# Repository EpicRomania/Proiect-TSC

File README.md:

# Proiect-TSC

## Block Diagram

## ESP32-C6

Microcontrolerul central care coordoneaza procesarea datelor si comunicarea cu modulele.
- Microcontroler RISC-V cu Wi-Fi 6 și Bluetooth LE.
  
**Controleaza interfetele SPI si I2C pentru restul modulelor.**

**Pentru conectarea memoriei externe, sunt folositi urmatorii pini:**

- MOSI  
- MISO  
- SCK  
- CS

**Pentru conectarea ceasului real si a senzorilor, se utilizeaza:**

- SDA  
- SCL

**Pinii de debug si programare sunt accesibili prin interfata dedicata.**

## Memorie Externa

- Conectata prin SPI (MOSI, MISO, SCK, CS). 

- Stocheaza datele e-book si firmware-ul.

## Ceas Real si Module Senzoriale

- Dispozitivele de timp real si senzorii se conecteaza pe pinii SDA si SCL.
- **DS3231** pentru data/ora precisa (RTC).  
- **BME680/BME688** pentru temperatura, umiditate, presiune si VOC (aer). 
- Aceste module asigura sincronizarea si monitorizarea mediului.

## Afisaj E-Paper 
- Controlat prin interfata SPI (linii comune cu memoria externa, dar cu semnal CS separat).  
- Are propriul circuit driver (bobina L2 si componente auxiliare).

## Stocare pe card SD
- Conectat tot pe magistrala SPI pentru extinderea posibilitatilor de stocare

 ## Butoane  
- **Reset** si **Boot** pentru controlul microcontrolerului (reprogramare, reset).
- **Change** – buton suplimentar pentru interactiuni in aplicatie.

## Management Baterie
- **MCP73831** ca incarcator LiPo (5 V din USB-C -> LiPo).  
- **MAX17048** ca monitor de nivel al bateriei (I2C).  
- **USB-C** pentru alimentare, incarcare si, la nevoie, date USB.

## Aspecte de Design

- Componentele sunt asezate astfel incat accesul la conectori sa fie relatic simplu.
- Test pads (TP) sunt disponibile pe fata placii pentru masuratori de semnal si alimentare.  
- Circuitele de protectie ESD si de filtrare sunt incluse pentru USB-C si liniile SPI. 

## Bill of Materials

| Component                          | Buy Link                                                                                                      | Datasheet Link                                                                                                                 |
|------------------------------------|---------------------------------------------------------------------------------------------------------------|--------------------------------------------------------------------------------------------------------------------------------|
| ADAFRUIT_LEDCHIP-LED0603           | [Mouser](https://ro.mouser.com/c/optoelectronics/led-lighting/?m=Adafruit)                                    | [Datasheet](https://ro.mouser.com/c/optoelectronics/led-lighting/?m=Adafruit)                                                  |
| SJ                                 | [GrabCAD](https://grabcad.com/library/solder-jumpers-1)                                                       | [GrabCAD](https://grabcad.com/library/solder-jumpers-1)                                                                        |
| ESP32_WROVER_EAGLE-LTSPICE_CC0402  | [Mouser](https://ro.mouser.com/c/passive-components/capacitors/ceramic-capacitors/?q=CC0402)                  | [Datasheet](https://componentsearchengine.com/Datasheets/2/CC0402MRX5R5BB106.pdf)                                              |
| ESP32_WROVER_EAGLE-LTSPICE_RR0402  | [Mouser](https://ro.mouser.com/c/passive-components/resistors/smd-resistors-chip-resistors/?case%20code%20-%20in=0402) | [Datasheet](https://www.yageo.com/upload/media/product/products/datasheet/rchip/PYu-RC_Group_51_RoHS_L_12.pdf)                 |
| RCL_CPOL-EUCT3528                  | [Mouser](https://ro.mouser.com/c/passive-components/antennas/?m=Linx+Technologies&series=RCL)                 | [Mouser](https://ro.mouser.com/c/passive-components/antennas/?m=Linx+Technologies&series=RCL)                                  |
| 112A-TAAR-R03_ATTEND               | [Comet](https://store.comet.srl.ro/Catalogue/Product/43497/)                                                   | [SnapEDA](https://www.snapeda.com/parts/112A-TAAR-R03/Attend/datasheet/)                                                       |
| DMG2305UX-7                        | [DigiKey](https://www.digikey.com/en/products/detail/diodes-incorporated/DMG2305UX-7/4340666)                 | [Datasheet](https://www.diodes.com/assets/Datasheets/DMG2305UX.pdf)                                                            |
| 744043680IND_4828-WE-TPC_WRE       | [Mouser](https://ro.mouser.com/ProductDetail/Wurth-Elektronik/744043680?qs=PGXP4M47uW6VkZq%252BkzjrHA%3D%3D)  | [Datasheet](https://www.we-online.com/components/products/datasheet/744043680.pdf)                                             |
| BME680                             | [Mouser](https://ro.mouser.com/ProductDetail/Bosch-Sensortec/BME688?qs=IS%252B4QmGtzzqQoVDscqwx3A%3D%3D)      | [Datasheet](https://ro.mouser.com/datasheet/2/783/bst_bme688_fl000-2307034.pdf)                                                |
| BUTTON_CUSYOMV1                    | [Panasonic](https://industry.panasonic.com/global/en/products/control/switch/light-touch/number/evqpuj02k)    | [Datasheet](https://industry.panasonic.com/global/en/downloads?tab=catalog&small_g_cd=203&part_no=EVQPUJ02K)                   |
| DS3231SN#                          | [Mouser](https://ro.mouser.com/ProductDetail/Analog-Devices-Maxim-Integrated/DS3231SN?qs=1eQvB6Dk1vhUlr8%2FOrV0Fw%3D%3D) | [Datasheet](https://ro.mouser.com/datasheet/2/609/DS3231-3421123.pdf)                                                          |
| ESP32-C6-WROOM-1-N8                | [Mouser](https://ro.mouser.com/ProductDetail/Espressif-Systems/ESP32-C6-WROOM-1-N8?qs=8Wlm6%252BaMh8ST02Gmwp74cw%3D%3D) | [Datasheet](https://ro.mouser.com/datasheet/2/891/Espressif_ESP32_C6_WROOM_1__Datasheet_V0_1_PRELIMI-3239987.pdf)              |
| ESP32C6_VARISTORCN1812             | [Mouser](https://ro.mouser.com/c/circuit-protection/varistors/?package=1812)                                 | [Mouser](https://ro.mouser.com/c/circuit-protection/varistors/?package=1812)                                                   |
| SD0805S020S1R0                     | [Mouser](https://ro.mouser.com/ProductDetail/KYOCERA-AVX/SD0805S020S1R0?qs=jCA%252BPfw4LHbpkAoSnwrdjw%3D%3D)  | [Datasheet](https://ro.mouser.com/datasheet/2/40/schottky-3165252.pdf)                                                         |
| MCP73831                           | [Mouser](https://ro.mouser.com/ProductDetail/Microchip-Technology/MCP73831T-2ATI-OT?qs=yUQqVecv4qsZbioEUu%252B83g%3D%3D) | [Datasheet](https://ro.mouser.com/datasheet/2/268/MCP73831_Family_Data_Sheet_DS20001984H-3441711.pdf)                          |

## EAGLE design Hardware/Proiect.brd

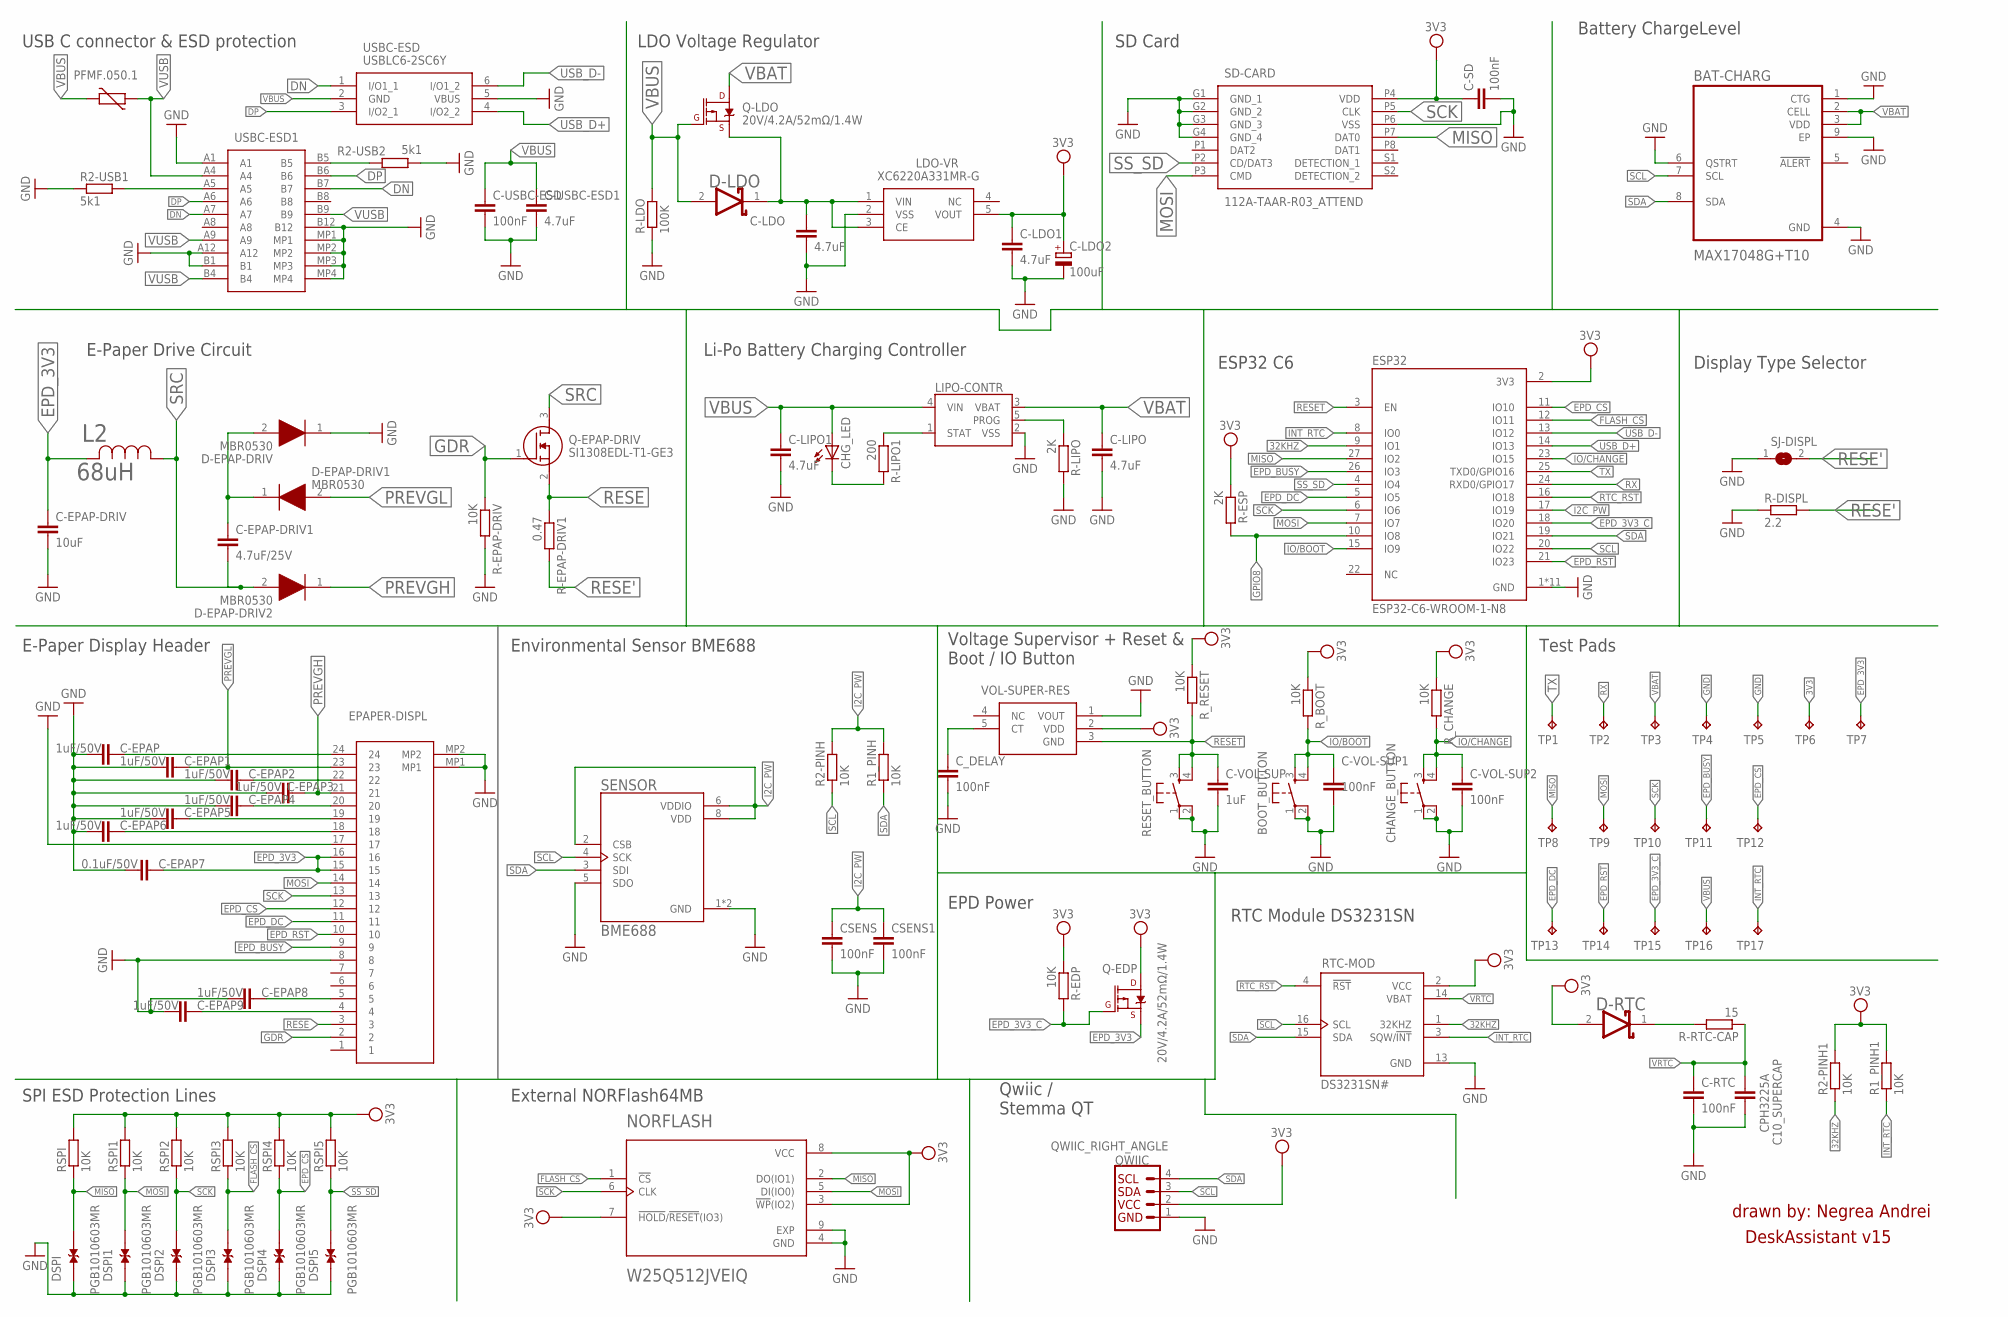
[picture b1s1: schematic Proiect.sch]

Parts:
BAT-CHARG: MAX17048G+T10; SON50P200X200X80-9N
BOOT_BUTTON: BOOT_BUTTON; MYBUTTON
C-EPAP, C-EPAP1, C-EPAP2, C-EPAP3, C-EPAP4, C-EPAP5, C-EPAP6, C-EPAP8, C-EPAP9: 1uF/50V; ESP32_WROVER_EAGLE-LTSPICE_C0402
C-EPAP7: 0.1uF/50V; ESP32_WROVER_EAGLE-LTSPICE_C0402
C-EPAP-DRIV: 10uF; ESP32_WROVER_EAGLE-LTSPICE_C0402
C-EPAP-DRIV1: 4.7uF/25V; ESP32_WROVER_EAGLE-LTSPICE_C0402
C-LDO, C-LDO1: 4.7uF; ESP32_WROVER_EAGLE-LTSPICE_C0402
C-LDO2: 100uF; RCL_CT3528
C-LIPO, C-LIPO1: 4.7uF; ESP32_WROVER_EAGLE-LTSPICE_C0402
C-RTC: 100nF; ESP32_WROVER_EAGLE-LTSPICE_C0402
C-SD: 100nF; ESP32_WROVER_EAGLE-LTSPICE_C0402
C-USBC-ESD: 100nF; ESP32_WROVER_EAGLE-LTSPICE_C0402
C-USBC-ESD1: 4.7uF; ESP32_WROVER_EAGLE-LTSPICE_C0402
C-VOL-SUP: 1uF; ESP32_WROVER_EAGLE-LTSPICE_C0402
C-VOL-SUP1, C-VOL-SUP2: 100nF; ESP32_WROVER_EAGLE-LTSPICE_C0402
CHANGE_BUTTON: CHANGE_BUTTON; MYBUTTON
CHG_LED: ADAFRUIT_LEDCHIP-LED0603; ADAFRUIT_CHIP-LED0603
CPH3225A: C10_SUPERCAP; ESP32_WROVER_EAGLE-LTSPICE_C0402
CSENS, CSENS1: 100nF; ESP32_WROVER_EAGLE-LTSPICE_C0402
C_DELAY: 100nF; ESP32_WROVER_EAGLE-LTSPICE_C0402
D-EPAP-DRIV, D-EPAP-DRIV1, D-EPAP-DRIV2: MBR0530; SOD3716X135N
D-LDO: ESP32_WROVER_AVX---SD0805S020S1R0_AVX_SD0805S020S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; ESP32_WROVER_AVX---SD0805S020S1R0_AVX_SD0805S020S1R0_0
D-RTC: ESP32_WROVER_AVX---SD0805S020S1R0_AVX_SD0805S020S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; ESP32_WROVER_AVX---SD0805S020S1R0_AVX_SD0805S020S1R0_0
DSPI, DSPI1, DSPI2, DSPI3, DSPI4, DSPI5: PGB1010603MR; DIOC1608X36N
EPAPER-DISPL: FH34SRJ-24S-0.5SH_99_; FH34SRJ24S05SH99
ESP32: ESP32-C6-WROOM-1-N8; XCVR_ESP32-C6-WROOM-1-N8
L2: 68uH; IND_4828-WE-TPC_WRE
LDO-VR: XC6220A331MR-G; SOT95P280X120-5N
LIPO-CONTR: ESP32_WROVER_SPARKFUN-IC-POWER_MCP73831; ESP32_WROVER_SPARKFUN-IC-POWER_SOT23-5
NORFLASH: W25Q512JVEIQ; SON127P600X800X80-9N
PFMF.050.1: ESP32C6_VARISTORCN1812; ESP32C6_VARISTOR_CT/CN1812
Q-EDP: 20V/4.2A/52mΩ/1.4W; ESP32_WROVER_SPARKFUN-DISCRETESEMI_SOT23-3
Q-EPAP-DRIV: SI1308EDL-T1-GE3; SOT65P210X110-3N
Q-LDO: 20V/4.2A/52mΩ/1.4W; ESP32_WROVER_SPARKFUN-DISCRETESEMI_SOT23-3
QWIIC: QWIIC_RIGHT_ANGLE; JST04_1MM_RA
R1_PINH, R1_PINH1, R2-PINH, R2-PINH1: 10K; ESP32_WROVER_EAGLE-LTSPICE_R0402
R2-USB1, R2-USB2: 5k1; ESP32_WROVER_EAGLE-LTSPICE_R0402
R-DISPL: 2.2; ESP32_WROVER_EAGLE-LTSPICE_R0402
R-EDP: 10K; ESP32_WROVER_EAGLE-LTSPICE_R0402
R-EPAP-DRIV: 10K; ESP32_WROVER_EAGLE-LTSPICE_R0402
R-EPAP-DRIV1: 0.47; ESP32_WROVER_EAGLE-LTSPICE_R0402
R-ESP: 2K; ESP32_WROVER_EAGLE-LTSPICE_R0402
R-LDO: 100K; ESP32_WROVER_EAGLE-LTSPICE_R0402
R-LIPO: 2K; ESP32_WROVER_EAGLE-LTSPICE_R0402
R-LIPO1: 200; ESP32_WROVER_EAGLE-LTSPICE_R0402
R-RTC-CAP: 15; ESP32_WROVER_EAGLE-LTSPICE_R0402
RESET_BUTTON: RESET_BUTTON; MYBUTTON
RSPI, RSPI1, RSPI2, RSPI3, RSPI4, RSPI5: 10K; ESP32_WROVER_EAGLE-LTSPICE_R0402
RTC-MOD: DS3231SN#; SOIC127P1032X265-16N
R_BOOT: 10K; ESP32_WROVER_EAGLE-LTSPICE_R0402
R_CHANGE: 10K; ESP32_WROVER_EAGLE-LTSPICE_R0402
R_RESET: 10K; ESP32_WROVER_EAGLE-LTSPICE_R0402
SD-CARD: 112A-TAAR-R03_ATTEND; 112ATAARR03ATTEND
SENSOR: BME688; ESP32_WROVER_BME680_PSON80P300X300X100-8N
SJ-DISPL: SJ
TP1, TP2, TP3, TP4, TP5, TP6, TP7, TP8, TP9, TP10, TP11, TP12, TP13, TP14, TP15, TP16, TP17: TPTP20R; TP20R
USBC-ESD: USBLC6-2SC6Y; SOT95P280X145-6N
USBC-ESD1: SAMACSYS_PARTS_USB4110-GF-A; SAMACSYS_PARTS_USB4110GFA
VOL-SUPER: VOL-SUPER-RES; SOT95P280X125-5N

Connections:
3V3: C-LDO1.1, C-LDO2.+, C-SD.1, D-RTC.2 (ANODE), ESP32.2 (3V3), LDO-VR.5 (VOUT), NORFLASH.3 (!WP!(IO2)), NORFLASH.7 (!HOLD!/!RESET!(IO3)), NORFLASH.8 (VCC), Q-EDP.3 (D), QWIIC.2, R1_PINH1.2, R2-PINH1.2, R-EDP.1, R-ESP.1, RSPI.2, RSPI1.2, RSPI2.2, RSPI3.2, RSPI4.2, RSPI5.2, RTC-MOD.2 (VCC), R_BOOT.1, R_CHANGE.1, R_RESET.1, SD-CARD.P4 (VDD), TP6.TP, VOL-SUPER.2 (VDD)
32KHZ: ESP32.9 (IO1), R2-PINH1.1, RTC-MOD.1 (32KHZ)
DN: USBC-ESD.1 (I/O1_1), USBC-ESD1.A7, USBC-ESD1.B7
DP: USBC-ESD.3 (I/O2_1), USBC-ESD1.A6, USBC-ESD1.B6
EPD_3V3: C-EPAP7.1, C-EPAP-DRIV.1, EPAPER-DISPL.15, EPAPER-DISPL.16, L2.2, Q-EDP.2 (S), TP7.TP
EPD_3V3_C: ESP32.18 (IO20), Q-EDP.1 (G), R-EDP.2, TP15.TP
EPD_BUSY: EPAPER-DISPL.9, ESP32.26 (IO3), TP11.TP
EPD_CS: DSPI4.2, EPAPER-DISPL.12, ESP32.11 (IO10), RSPI4.1, TP12.TP
EPD_DC: EPAPER-DISPL.11, ESP32.5 (IO5), TP13.TP
EPD_RST: EPAPER-DISPL.10, ESP32.21 (IO23), TP14.TP
FLASH_CS: DSPI3.2, ESP32.12 (IO11), NORFLASH.1 (!CS), RSPI3.1
GDR: EPAPER-DISPL.2, Q-EPAP-DRIV.1 (G), R-EPAP-DRIV.1
GND: BAT-CHARG.1 (CTG), BAT-CHARG.4 (GND), BAT-CHARG.6 (QSTRT), BAT-CHARG.9 (EP), BOOT_BUTTON.1, BOOT_BUTTON.2, C-EPAP.2, C-EPAP1.2, C-EPAP2.2, C-EPAP3.2, C-EPAP4.2, C-EPAP5.2, C-EPAP6.2, C-EPAP7.2, C-EPAP8.2, C-EPAP9.2, C-EPAP-DRIV.2, C-LDO.2, C-LDO1.2, C-LDO2.-, C-LIPO.2, C-LIPO1.2, C-RTC.2, C-SD.2, C-USBC-ESD.2, C-USBC-ESD1.2, C-VOL-SUP.2, C-VOL-SUP1.2, C-VOL-SUP2.2, CHANGE_BUTTON.1, CHANGE_BUTTON.2, CPH3225A.2, CSENS.2, CSENS1.2, C_DELAY.2, D-EPAP-DRIV.1 (K), DSPI.1, DSPI1.1, DSPI2.1, DSPI3.1, DSPI4.1, DSPI5.1, EPAPER-DISPL.8, EPAPER-DISPL.17, EPAPER-DISPL.MP1, EPAPER-DISPL.MP2, ESP32.1 (GND), ESP32.28 (GND), ESP32.29_1 (GND), ESP32.29_2 (GND), ESP32.29_3 (GND), ESP32.29_4 (GND), ESP32.29_5 (GND), ESP32.29_6 (GND), ESP32.29_7 (GND), ESP32.29_8 (GND), ESP32.29_9 (GND), LDO-VR.2 (VSS), LIPO-CONTR.2 (VSS), NORFLASH.4 (GND), NORFLASH.9 (EXP), QWIIC.1, R2-USB1.1, R2-USB2.2, R-DISPL.1, R-EPAP-DRIV.2, R-LDO.1, R-LIPO.2, RESET_BUTTON.1, RESET_BUTTON.2, RTC-MOD.13 (GND), SD-CARD.G1 (GND_1), SD-CARD.G2 (GND_2), SD-CARD.G3 (GND_3), SD-CARD.G4 (GND_4), SD-CARD.P6 (VSS), SENSOR.1 (GND), SENSOR.5 (SDO), SENSOR.7 (GND), SJ-DISPL.1, TP4.TP, TP5.TP, USBC-ESD.5 (VBUS), USBC-ESD1.A1, USBC-ESD1.A12, USBC-ESD1.B1, USBC-ESD1.B12, USBC-ESD1.MP1, USBC-ESD1.MP2, USBC-ESD1.MP3, USBC-ESD1.MP4, VOL-SUPER.1 (VOUT)
GPIO8: ESP32.10 (IO8), R-ESP.2
I2C_PW: CSENS.1, CSENS1.1, ESP32.17 (IO19), R1_PINH.2, R2-PINH.2, SENSOR.2 (CSB), SENSOR.6 (VDDIO), SENSOR.8 (VDD)
INT_RTC: ESP32.8 (IO0), R1_PINH1.1, RTC-MOD.3 (SQW/!INT), TP17.TP
IO/BOOT: BOOT_BUTTON.3, BOOT_BUTTON.4, C-VOL-SUP1.1, ESP32.15 (IO9), R_BOOT.2
IO/CHANGE: C-VOL-SUP2.1, CHANGE_BUTTON.3, CHANGE_BUTTON.4, ESP32.23 (IO15), R_CHANGE.2
MISO: DSPI.2, ESP32.27 (IO2), NORFLASH.2 (DO(IO1)), RSPI.1, SD-CARD.P7 (DAT0), TP8.TP
MOSI: DSPI1.2, EPAPER-DISPL.14, ESP32.7 (IO7), NORFLASH.5 (DI(IO0)), RSPI1.1, SD-CARD.P3 (CMD), TP9.TP
unnamed: R2-USB1.2, USBC-ESD1.A5
unnamed: R2-USB2.1, USBC-ESD1.B5
unnamed: C-EPAP.1, EPAPER-DISPL.24
unnamed: CHG_LED.C, R-LIPO1.2
unnamed: LIPO-CONTR.1 (STAT), R-LIPO1.1
unnamed: LIPO-CONTR.5 (PROG), R-LIPO.1
unnamed: C-EPAP2.1, EPAPER-DISPL.22
unnamed: C-EPAP-DRIV1.1, D-EPAP-DRIV.2 (A), D-EPAP-DRIV1.1 (K)
unnamed: C-EPAP4.1, EPAPER-DISPL.20
unnamed: C-EPAP5.1, EPAPER-DISPL.19
unnamed: C-EPAP6.1, EPAPER-DISPL.18
unnamed: C_DELAY.1, VOL-SUPER.5 (CT)
unnamed: C-EPAP8.1, EPAPER-DISPL.5
unnamed: C-EPAP9.1, EPAPER-DISPL.4
unnamed: C-LDO.1, D-LDO.1 (CATHODE), LDO-VR.1 (VIN), LDO-VR.3 (CE), Q-LDO.2 (S)
unnamed: D-RTC.1 (CATHODE), R-RTC-CAP.2
PREVGH: C-EPAP3.1, D-EPAP-DRIV2.1 (K), EPAPER-DISPL.21
PREVGL: C-EPAP1.1, D-EPAP-DRIV1.2 (A), EPAPER-DISPL.23
RESE: EPAPER-DISPL.3, Q-EPAP-DRIV.2 (S), R-EPAP-DRIV1.1
RESE': R-DISPL.2, R-EPAP-DRIV1.2, SJ-DISPL.2
RESET: C-VOL-SUP.1, ESP32.3 (EN), RESET_BUTTON.3, RESET_BUTTON.4, R_RESET.2, VOL-SUPER.3 (GND)
RTC_RST: ESP32.16 (IO18), RTC-MOD.4 (!RST)
RX: ESP32.24 (RXD0/GPIO17), TP2.TP
SCK: DSPI2.2, EPAPER-DISPL.13, ESP32.6 (IO6), NORFLASH.6 (CLK), RSPI2.1, SD-CARD.P5 (CLK), TP10.TP
SCL: BAT-CHARG.7 (SCL), ESP32.20 (IO22), QWIIC.3, R2-PINH.1, RTC-MOD.16 (SCL), SENSOR.4 (SCK)
SDA: BAT-CHARG.8 (SDA), ESP32.19 (IO21), QWIIC.4, R1_PINH.1, RTC-MOD.15 (SDA), SENSOR.3 (SDI)
SRC: C-EPAP-DRIV1.2, D-EPAP-DRIV2.2 (A), L2.1, Q-EPAP-DRIV.3 (D)
SS_SD: DSPI5.2, ESP32.4 (IO4), RSPI5.1, SD-CARD.P2 (CD/DAT3)
TX: ESP32.25 (TXD0/GPIO16), TP1.TP
USB_D+: ESP32.14 (IO13), USBC-ESD.4 (I/O2_2)
USB_D-: ESP32.13 (IO12), USBC-ESD.6 (I/O1_2)
VBAT: BAT-CHARG.2 (CELL), BAT-CHARG.3 (VDD), C-LIPO.1, LIPO-CONTR.3 (VBAT), Q-LDO.3 (D), TP3.TP
VBUS: C-LIPO1.1, C-USBC-ESD.1, C-USBC-ESD1.1, CHG_LED.A, D-LDO.2 (ANODE), LIPO-CONTR.4 (VIN), PFMF.050.1.2, Q-LDO.1 (G), R-LDO.2, TP16.TP, USBC-ESD.2 (GND)
VRTC: C-RTC.1, CPH3225A.1, R-RTC-CAP.1, RTC-MOD.14 (VBAT)
VUSB: PFMF.050.1.1, USBC-ESD1.A4, USBC-ESD1.A9, USBC-ESD1.B4, USBC-ESD1.B9

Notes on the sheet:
USB C connector & ESD protection
LDO Voltage Regulator
SD Card
Display Type Selector
E-Paper Drive Circuit
Li-Po Battery Charging Controller
ESP32 C6
E-Paper Display Header
EPD Power
Environmental Sensor BME688
Voltage Supervisor + Reset & Boot / IO Button
Battery ChargeLevel
RTC Module DS3231SN
Test Pads
Qwiic / Stemma QT
SPI ESD Protection Lines
External NORFlash64MB
drawn by: Negrea Andrei
DeskAssistant v15

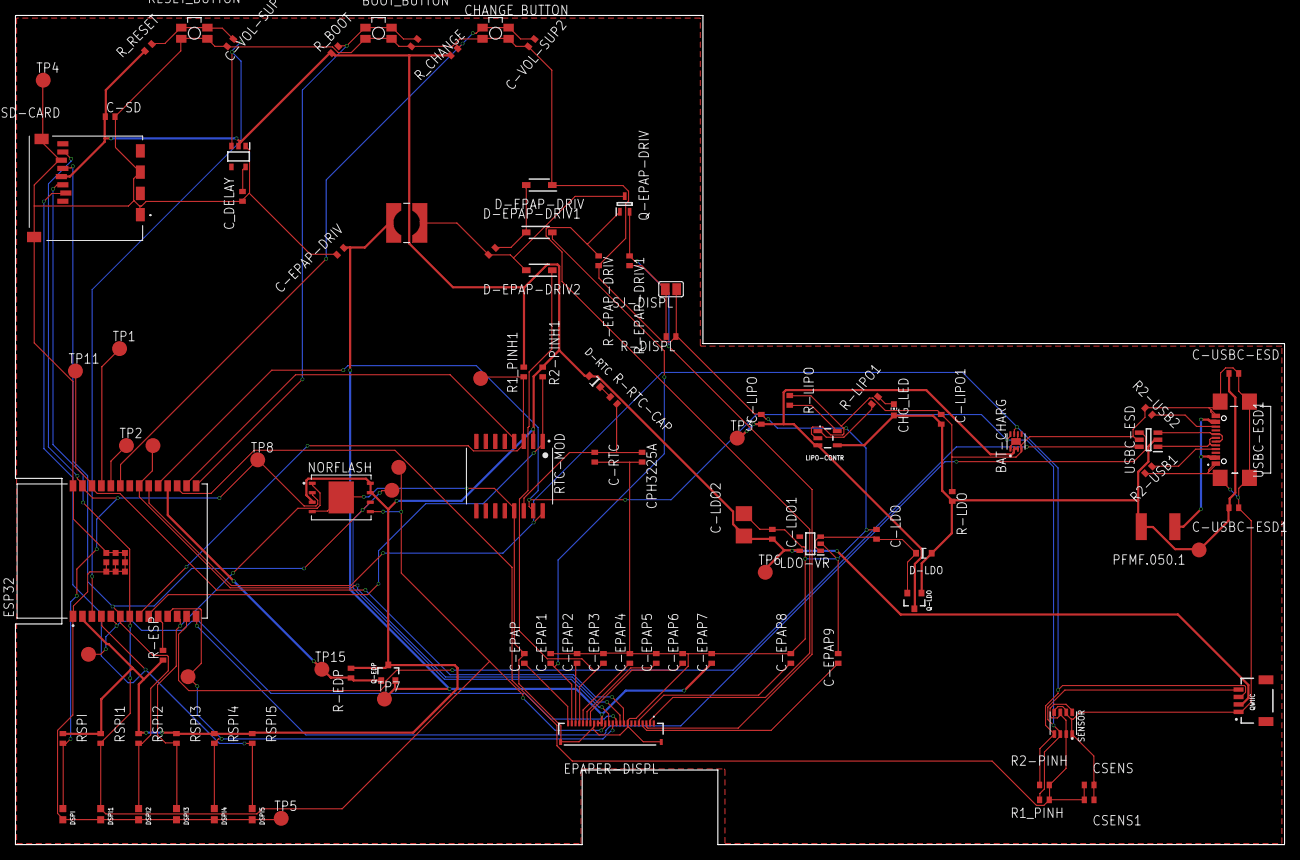
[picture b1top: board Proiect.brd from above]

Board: 2 copper layers, 170.2 x 111.2 mm, 103 parts (0 on the bottom side), 55 nets.

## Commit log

2025-04-08 Create Hardware
2025-04-08 Create x
2025-04-15 Create LICENSE

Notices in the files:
parts and their libraries:
COPYRIGHT: Copyright (C) 2024 Ultra Librarian. All rights reserved.
